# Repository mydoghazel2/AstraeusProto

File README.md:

# Astraeus

This is the github repo of the West Virginia University SRAD avionics project named Astraeus.

Astreaus is a student led project to develop cheap, open-source, and modular avionics. The goal is to create electronics for our competition rocket and for student use on personal rockets. 

Astraeus is the greek god of the wind and dusk to match not only the idea of our avionics being on a rocket but also our competition rocket being named "Dark and Dusty" after the song Country Roads 

# Final Design 
## Top Side

## Bottom Side 

# PCB

EAGLE is used as the PCB designing software. All the libraries needed is included in `./PCB/lib`

- if you are on linux. Use the following command to make a sim links to the default eagle save directory  

```
ln -s ./PCB $HOME/EAGLE/projects/git-pcb
```

- if you are on windows 10: Add instructions on how to get EAGLE running

# TO-DO

- [x] Initial planning and requirement gathering.
- [x] Finalizing the hardware specification.
- [x] Schematic design
  - [x] BMS
  - [x] voltage regulation
  - [x] Sensors
  - [x] USB
  - [ ] upload/download
  - [ ] SD card

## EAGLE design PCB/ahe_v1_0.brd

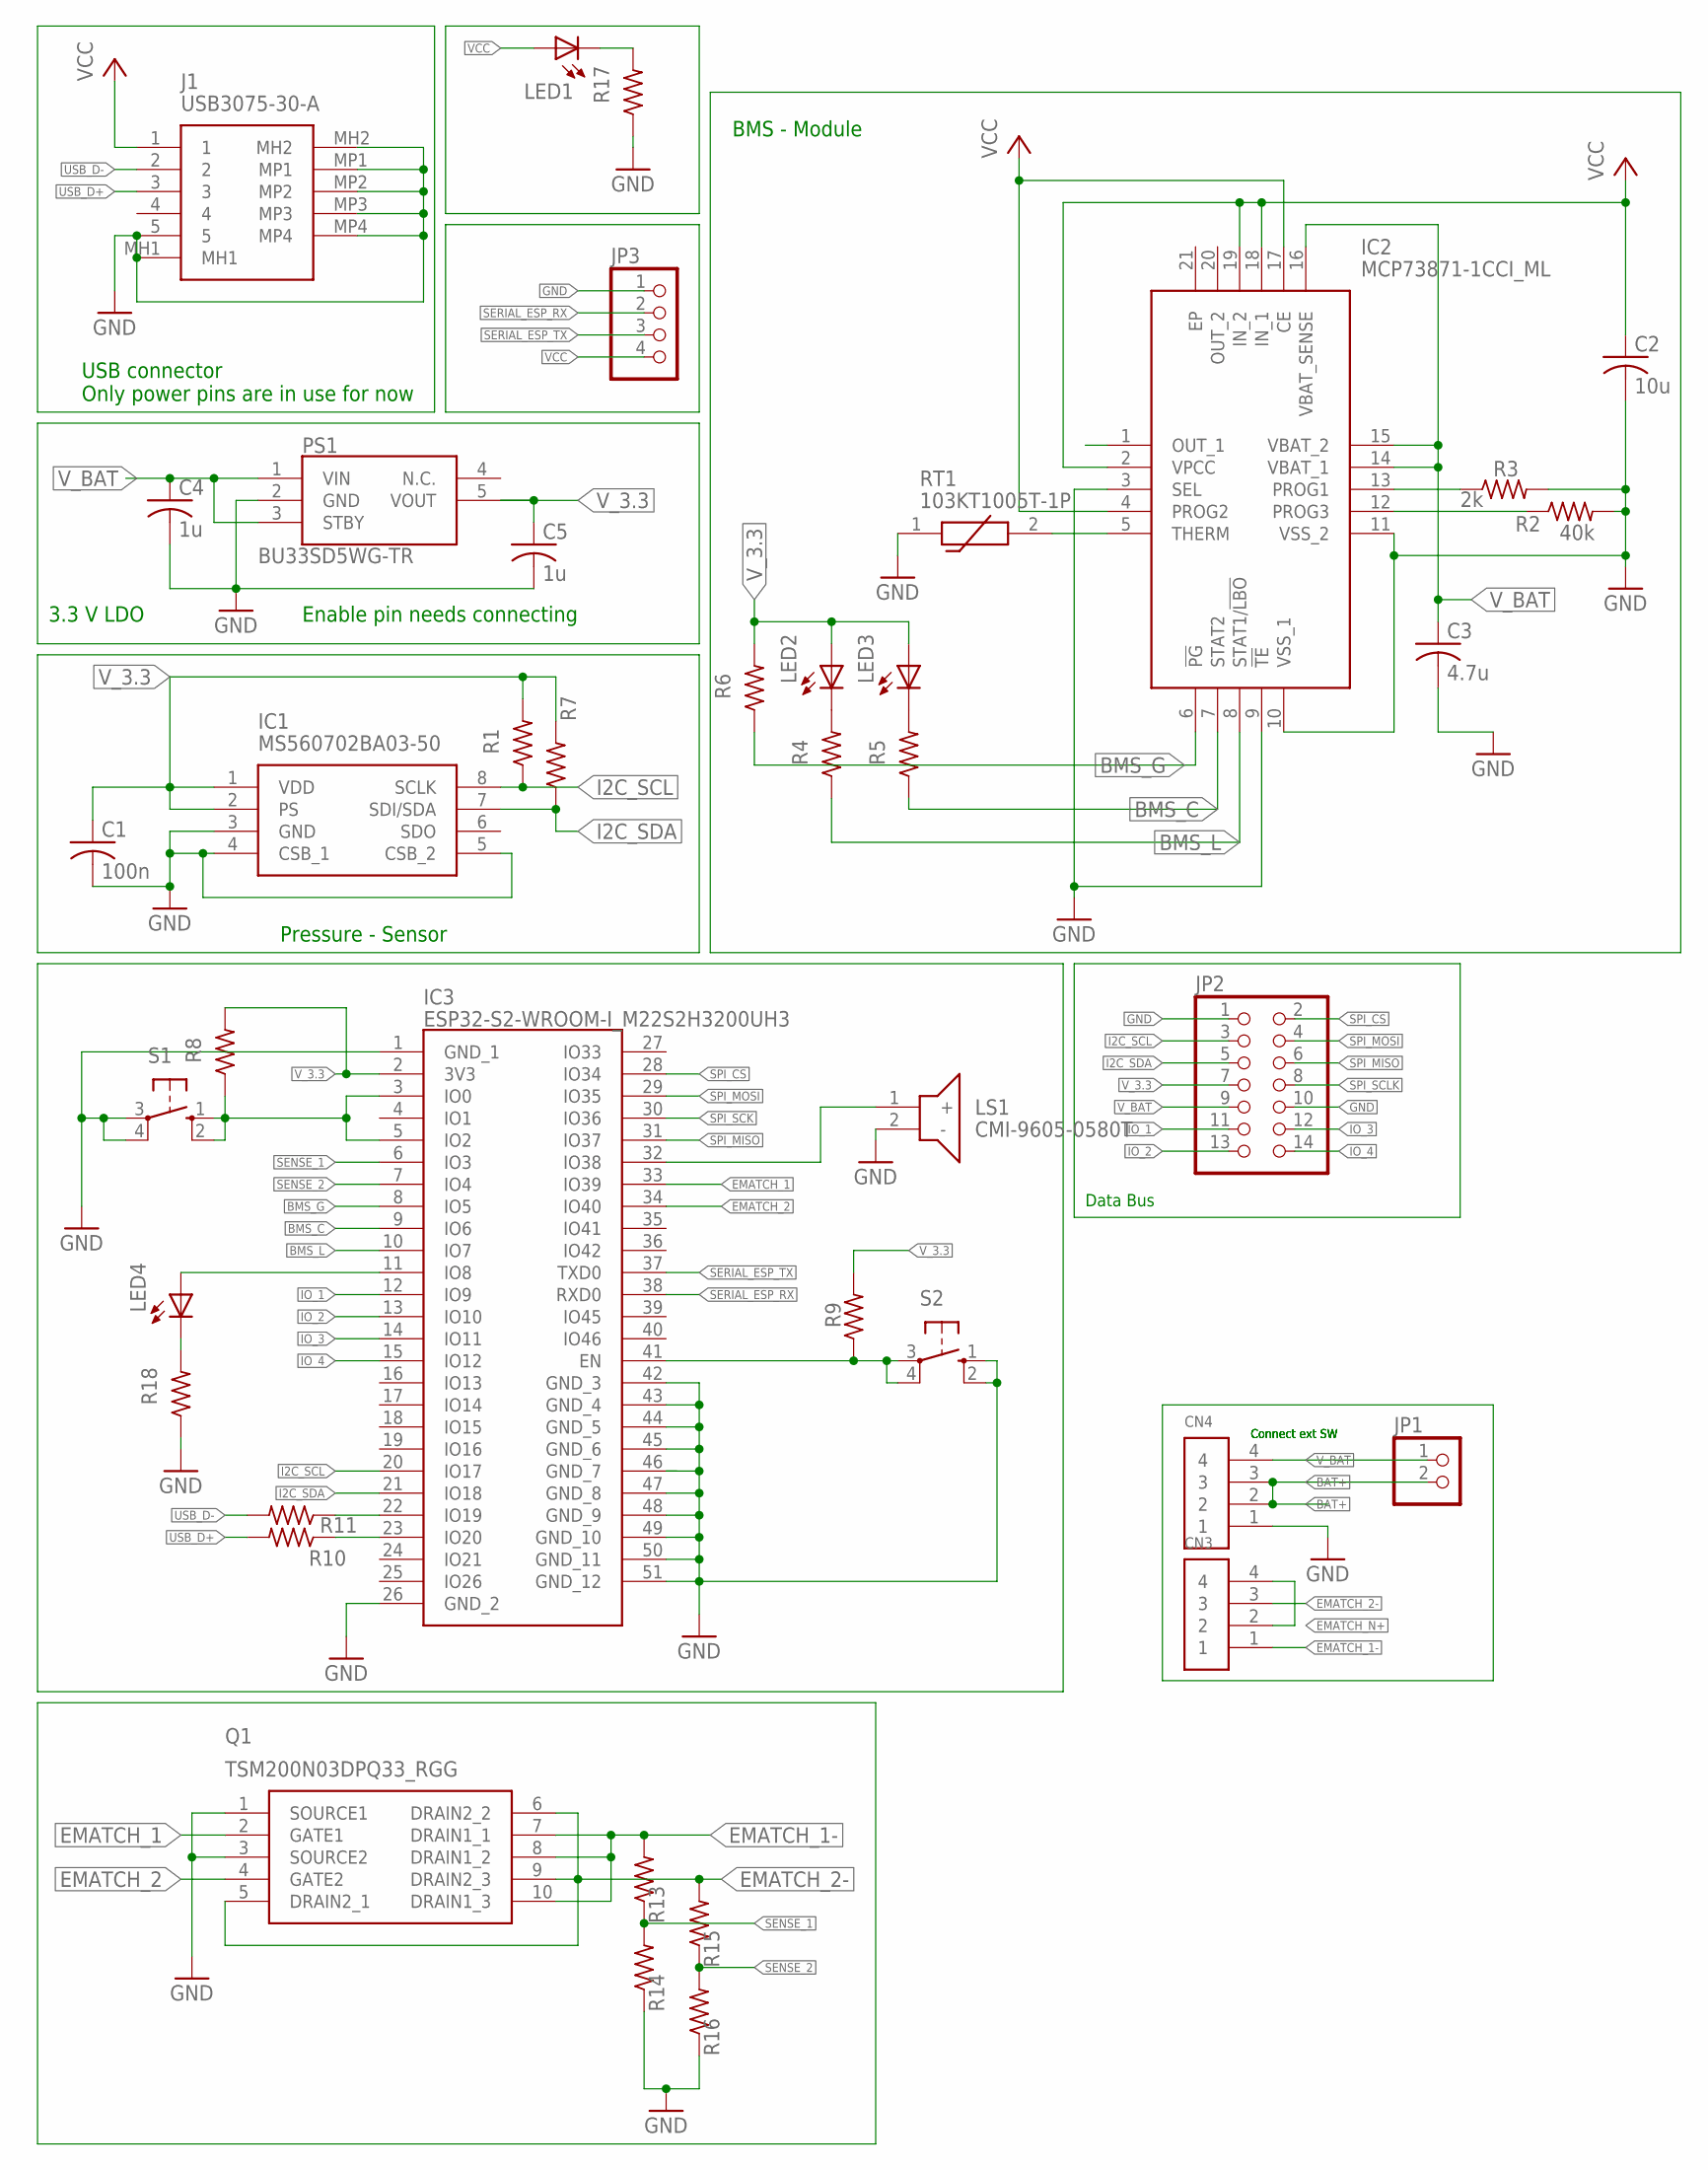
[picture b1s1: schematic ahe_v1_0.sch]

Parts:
C1: 100n; C0805
C2: 10u; C0805
C3: 4.7u; C0805
C4, C5: 1u; C0805
CN3, CN4: 1X4-3.5MM; 1X04-3.5MM
IC1: MS560702BA03-50; MS5607-02BA03
IC2: MCP73871-1CCI_ML; QFN50P400X400X100-21N
IC3: ESP32-S2-WROOM-I_M22S2H3200UH3; ESP32S2WROOMIM22S2H3200UH3Q0
J1: USB3075-30-A; USB307530A
JP1: PINHD-1X2; 1X02
JP2: PINHD-2X7; 2X07
JP3: PINHD-1X4/90; 1X04/90
LED1, LED2, LED3, LED4: LEDCHIPLED_0805; CHIPLED_0805
LS1: CMI-9605-0580T; CMI96050580T
PS1: BU33SD5WG-TR; SOT95P280X125-5N
Q1: TSM200N03DPQ33_RGG; TSM200N03DPQ33RGG
R1, R6, R7, R8, R9: 10k; R0805
R2: 40k; R0805
R3: 2k; R0805
R4, R5, R17, R18: 330; R0805
R10, R11: 33; R0805
R13, R15: 100k; R0805
R14, R16: 27k; R0805
RT1: 103KT1005T-1P; THRMC1005X60N
S1, S2: 10-XX; B3F-10XX

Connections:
BAT+: CN4.2, CN4.3, JP1.2
BMS_C: IC2.7 (STAT2), IC3.9 (IO6), R5.1
BMS_G: IC2.6 (!PG), IC3.8 (IO5), R6.1
BMS_L: IC2.8 (STAT1/!LBO), IC3.10 (IO7), R4.1
EMATCH_1: IC3.33 (IO39), Q1.2 (GATE1)
EMATCH_1-: CN3.1, Q1.7 (DRAIN1_1), Q1.8 (DRAIN1_2), Q1.10 (DRAIN1_3), R13.2
EMATCH_2: IC3.34 (IO40), Q1.4 (GATE2)
EMATCH_2-: CN3.3, Q1.5 (DRAIN2_1), Q1.6 (DRAIN2_2), Q1.9 (DRAIN2_3), R15.2
EMATCH_N+: CN3.2, CN3.4
I2C_SCL: IC1.8 (SCLK), IC3.20 (IO17), JP2.3, R1.1
I2C_SDA: IC1.7 (SDI/SDA), IC3.21 (IO18), JP2.5, R7.1
IO_1: IC3.12 (IO9), JP2.11
IO_2: IC3.13 (IO10), JP2.13
IO_3: IC3.14 (IO11), JP2.12
IO_4: IC3.15 (IO12), JP2.14
unnamed: IC2.13 (PROG1), R3.1
unnamed: IC2.12 (PROG3), R2.1
unnamed 17: IC2.5 (THERM), RT1.2; also elsewhere on the board
unnamed: IC3.3 (IO0), IC3.5 (IO2), R8.1, S1.1 (S), S1.2 (S1)
unnamed: IC3.22 (IO19), R11.1
unnamed: IC3.23 (IO20), R10.1
unnamed: LED1.C, R17.2
unnamed: LED2.C, R4.2
unnamed: LED3.C, R5.2
unnamed: LED4.C, R18.2
unnamed: IC3.11 (IO8), LED4.A
SENSE_1: IC3.6 (IO3), R13.1, R14.2
SENSE_2: IC3.7 (IO4), R15.1, R16.2
SERIAL_ESP_RX: IC3.38 (RXD0), JP3.2; also elsewhere on the board
SERIAL_ESP_TX: IC3.37 (TXD0), JP3.3; also elsewhere on the board
SOUND: IC3.32 (IO38), LS1.1 (+)
SPI_CS: IC3.28 (IO34), JP2.2
SPI_MISO: IC3.31 (IO37), JP2.6
SPI_MOSI: IC3.29 (IO35), JP2.4
SPI_SCK: IC3.30 (IO36)
SPI_SCLK: JP2.8
USB_D+: J1.3, R10.2
USB_D-: J1.2, R11.2
VCC: C2.1, IC2.2 (VPCC), IC2.4 (PROG2), IC2.17 (CE), IC2.18 (IN_1), IC2.19 (IN_2), J1.1, JP3.4, LED1.A; also elsewhere on the board
V_3.3: C1.1, C5.1, IC1.1 (VDD), IC1.2 (PS), IC3.2 (3V3), JP2.7, LED2.A, LED3.A, PS1.5 (VOUT), R1.2, R6.2, R7.2, R8.2, R9.2
V_BAT: C3.1, C4.1, CN4.4, IC2.14 (VBAT_1), IC2.15 (VBAT_2), IC2.16 (VBAT_SENSE), JP1.1, JP2.9, PS1.1 (VIN), PS1.3 (STBY)

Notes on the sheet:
Pressure - Sensor
Enable pin needs connecting
USB connector Only power pins are in use for now
3.3 V LDO
BMS - Module
Data Bus
Connect ext SW

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
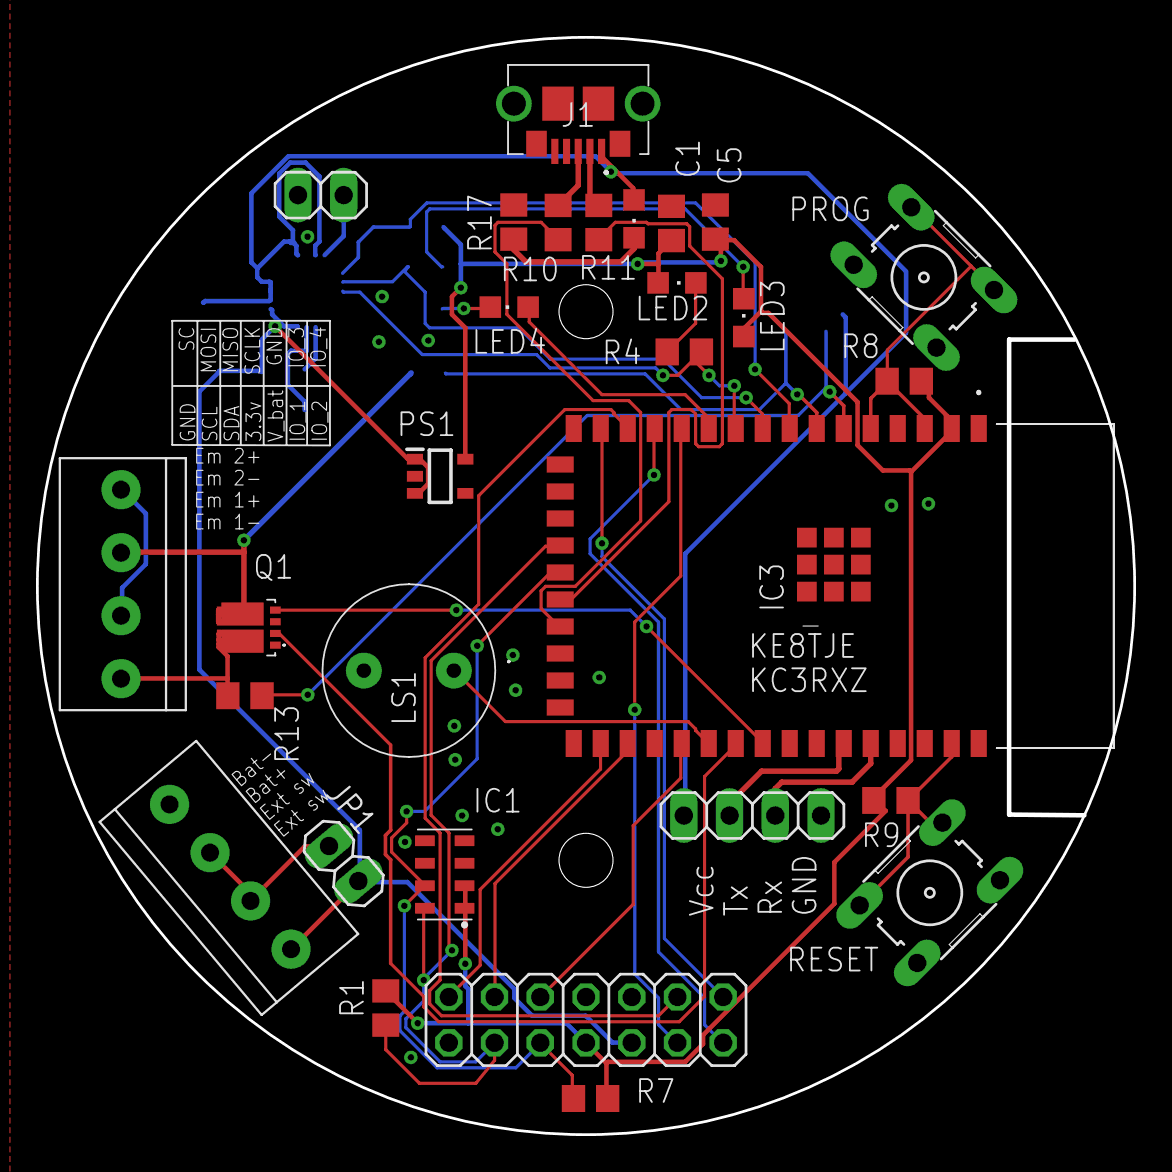
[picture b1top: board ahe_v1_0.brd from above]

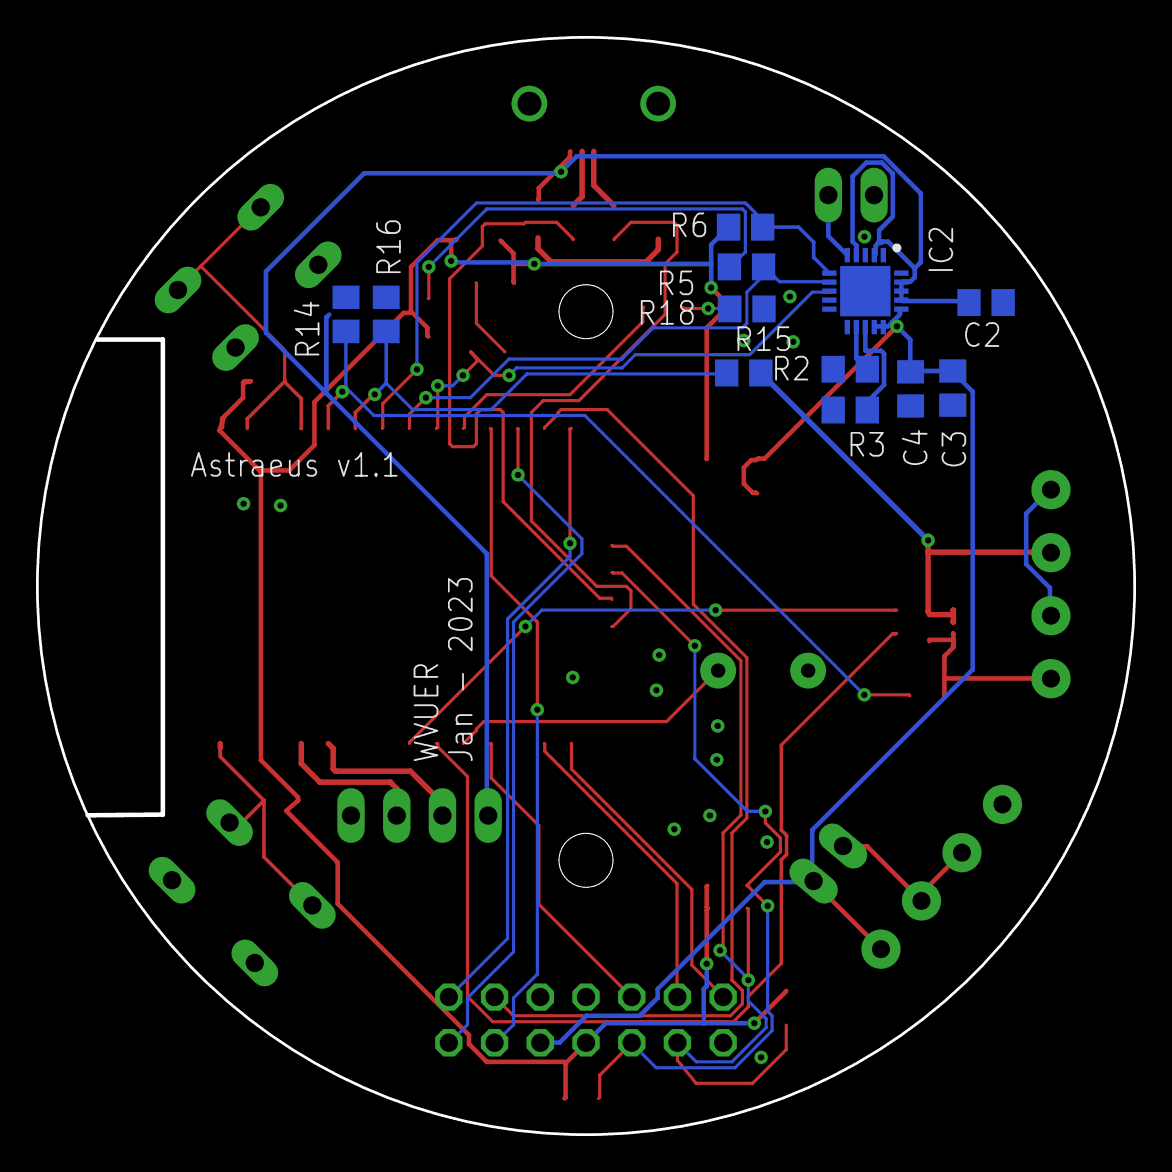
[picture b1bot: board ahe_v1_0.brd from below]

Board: 2 copper layers, 60.9 x 60.9 mm, 41 parts (12 on the bottom side), 41 nets.

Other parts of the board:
JP4: 1X02
JP5: 1X04

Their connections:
unnamed 17: JP4.2; also elsewhere on the board
SERIAL_ESP_RX: JP5.2; also elsewhere on the board
SERIAL_ESP_TX: JP5.3; also elsewhere on the board
VCC: JP5.4; also elsewhere on the board

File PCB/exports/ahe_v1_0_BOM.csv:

"Qty";"Value";"Device";"Package";"Parts";"Description";"ARROW_PART_NUMBER";"ARROW_PRICE-STOCK";"DESCRIPTION";"HEIGHT";"MANUFACTURER_NAME";"MANUFACTURER_PART_NUMBER";"MF";"MOUSER_PART_NUMBER";"MOUSER_PRICE-STOCK";"MOUSER_TESTING_PART_NUMBER";"MOUSER_TESTING_PRICE-STOCK";"MPN";"OC_FARNELL";"OC_NEWARK";"POPULARITY";"SPICEPREFIX";
"2";"";"10-XX";"B3F-10XX";"S1, S2";"OMRON SWITCH";"";"";"";"";"";"";"";"";"";"";"";"B3F-1000";"176432";"36M3542";"72";"";
"1";"";"PINHD-1X4/90";"1X04/90";"JP3";"PIN HEADER";"";"";"";"";"";"";"";"";"";"";"";"";"";"";"9";"";
"1";"";"PINHD-2X7";"2X07";"JP2";"PIN HEADER";"";"";"";"";"";"";"";"";"";"";"";"";"";"";"8";"";
"1";"0";"R-US_R0805";"R0805";"R12";"RESISTOR, American symbol";"";"";"";"";"";"";"";"";"";"";"";"";"";"";"85";"R";
"2";"100k";"R-US_R0805";"R0805";"R13, R15";"RESISTOR, American symbol";"";"";"";"";"";"";"";"";"";"";"";"";"";"";"85";"R";
"1";"100n";"C-USC0805";"C0805";"C1";"CAPACITOR, American symbol";"";"";"";"";"";"";"";"";"";"";"";"";"";"";"63";"C";
"1";"103KT1005T-1P";"103KT1005T-1P";"THRMC1005X60N";"RT1";"NTC Thermistors 103kohm 1% 0402";"";"";"NTC Thermistors 103kohm 1% 0402";"0.6mm";"Semitec";"103KT1005T-1P";"";"954-103KT1005T-1P";"https://www.mouser.co.uk/ProductDetail/Semitec/103KT1005T-1P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";"";"";"";"";"";"";"";
"7";"10k";"R-US_R0805";"R0805";"R1, R4, R5, R6, R7, R8, R9";"RESISTOR, American symbol";"";"";"";"";"";"";"";"";"";"";"";"";"";"";"85";"R";
"1";"10u";"C-USC0805";"C0805";"C2";"CAPACITOR, American symbol";"";"";"";"";"";"";"";"";"";"";"";"";"";"";"63";"C";
"2";"1X4-3.5MM";"1X4-3.5MM";"1X04-3.5MM";"CN1, CN2";"4-pin connector";"";"";"";"";"";"";"";"";"";"";"";"";"";"";"";"";
"2";"1u";"C-USC0805";"C0805";"C4, C5";"CAPACITOR, American symbol";"";"";"";"";"";"";"";"";"";"";"";"";"";"";"63";"C";
"2";"27k";"R-US_R0805";"R0805";"R14, R16";"RESISTOR, American symbol";"";"";"";"";"";"";"";"";"";"";"";"";"";"";"85";"R";
"1";"2k";"R-US_R0805";"R0805";"R3";"RESISTOR, American symbol";"";"";"";"";"";"";"";"";"";"";"";"";"";"";"85";"R";
"2";"33";"R-US_R0805";"R0805";"R10, R11";"RESISTOR, American symbol";"";"";"";"";"";"";"";"";"";"";"";"";"";"";"85";"R";
"1";"4.7u";"C-USC0805";"C0805";"C3";"CAPACITOR, American symbol";"";"";"";"";"";"";"";"";"";"";"";"";"";"";"63";"C";
"1";"40k";"R-US_R0805";"R0805";"R2";"RESISTOR, American symbol";"";"";"";"";"";"";"";"";"";"";"";"";"";"";"85";"R";
"1";"BU33SD5WG-TR";"BU33SD5WG-TR";"SOT95P280X125-5N";"PS1";"LDO regulator,3.3V,0.5A,standby,SSOP5 ROHM BU33SD5WG-TR, LDO Voltage Regulator, 0.5A, 3.3 V +/-2%, 1.7  6 Vin, 5-Pin SSOP";"";"";"LDO regulator,3.3V,0.5A,standby,SSOP5 ROHM BU33SD5WG-TR, LDO Voltage Regulator, 0.5A, 3.3 V +/-2%, 1.7  6 Vin, 5-Pin SSOP";"1.25mm";"ROHM Semiconductor";"BU33SD5WG-TR";"";"755-BU33SD5WG-TR";"https://www.mouser.co.uk/ProductDetail/ROHM-Semiconductor/BU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";"";"";"";"";"";"";"";
"1";"CMI-9605-0580T";"CMI-9605-0580T";"CMI96050580T";"LS1";"Piezo Buzzers & Audio Indicators buzzer, 9.6 mm x 5 mm deep, M, 5 VDC, 80 dB, Through Hole, Audio Indicator";"";"";"Piezo Buzzers & Audio Indicators buzzer, 9.6 mm x 5 mm deep, M, 5 VDC, 80 dB, Through Hole, Audio Indicator";"5mm";"CUI Inc.";"CMI-9605-0580T";"";"490-CMI-9605-0580T";"https://www.mouser.co.uk/ProductDetail/CUI-Devices/CMI-9605-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";"";"";"";"";"";"";"";
"1";"ESP32-S2-WROOM-I_M22S2H3200UH3";"ESP32-S2-WROOM-I_M22S2H3200UH3";"ESP32S2WROOMIM22S2H3200UH3Q0";"IC3";"WiFi Modules (802.11) Module ESP32-S2 WROOM IPEX ANT";"";"";"WiFi Modules (802.11) Module ESP32-S2 WROOM IPEX ANT";"3.45mm";"Espressif Systems";"ESP32-S2-WROOM-I(M22S2H3200UH3Q0)";"";"356-ESP32S2WRMI320UH";"https://www.mouser.co.uk/ProductDetail/Espressif-Systems/ESP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";"";"";"";"";"";"";"";
"1";"MCP73871-1CCI_ML";"MCP73871-1CCI_ML";"QFN50P400X400X100-21N";"IC2";"Battery Management USB/AC Battery Charger w/Pwr Mgmt";"";"";"Battery Management USB/AC Battery Charger w/Pwr Mgmt";"1mm";"Microchip";"MCP73871-1CCI/ML";"";"579-MCP73871-1CCI/ML";"https://www.mouser.co.uk/ProductDetail/Microchip-Technology-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";"";"";"";"";"";"";"";
"1";"MS560702BA03-50";"MS560702BA03-50";"MS5607-02BA03";"IC1";"MS560702BA03-50, Barometric Pressure Sensor, 1200mbar 0  3.6 V Output, 8-Pin QFN";"";"";"MS560702BA03-50, Barometric Pressure Sensor, 1200mbar 0  3.6 V Output, 8-Pin QFN";"mm";"TE Connectivity";"MS560702BA03-50";"";"824-MS560702BA03-50";"https://www.mouser.co.uk/ProductDetail/Measurement-Specialti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";"";"";"";"";"";"";"";
"1";"TSM200N03DPQ33_RGG";"TSM200N03DPQ33_RGG";"TSM200N03DPQ33RGG";"Q1";"MOSFET MOSFET, Dual, N-Ch Trench, 30V, 20A";"";"";"MOSFET MOSFET, Dual, N-Ch Trench, 30V, 20A";"0.8mm";"Taiwan Semiconductor";"TSM200N03DPQ33 RGG";"";"821-TSM200N03DPQ33RG";"https://www.mouser.co.uk/ProductDetail/Taiwan-Semiconductor/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";"";"";"";"";"";"";"";
"1";"USB3075-30-A";"USB3075-30-A";"USB307530A";"J1";"GCT (GLOBAL CONNECTOR TECHNOLOGY) - USB3075-30-A - USB Connector, Micro USB Type B, USB 2.0, Receptacle, 5 Ways, Surface Mount, Right Angle";"";"";"GCT (GLOBAL CONNECTOR TECHNOLOGY) - USB3075-30-A - USB Connector, Micro USB Type B, USB 2.0, Receptacle, 5 Ways, Surface Mount, Right Angle";"2.7mm";"GCT (GLOBAL CONNECTOR TECHNOLOGY)";"USB3075-30-A";"";"640-USB3075-30-A";"https://www.mouser.co.uk/ProductDetail/GCT/USB3075-30-A?qs=K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";"";"";"";"";"";"";"";

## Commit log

2022-09-23 Initial Commit with Proposal and Budget
2022-09-23 Fixed the readme md
2022-09-23 updated the readme with todo
2022-09-23 moved documentation to docs
2022-11-15 Added the eagel PCB project files to ./PCB
2022-11-15 updated the readme with eagle usage instructions
2022-11-15 Added the adafruit.lbr for basic components
2022-11-30 added an LDO
2022-12-01 added some cosmatics to completed parts
2022-12-09 Updated the BMS i/o
2022-12-09 modified BMS
2022-12-15 Completed BMS/LDO
2022-12-16 #6 pressure sensor completed
2022-12-17 updated the ESP32 library to match actual product
2022-12-17 remove old library
2022-12-18 #5 #2 added databus and basic IO
2022-12-18 full schematic
2022-12-18 added costing to the BOM
2022-12-20 added SPI from the ESP
2022-12-21 #2 board 1 with lipo mounted on the back
2022-12-21 added board file
2022-12-21 removed v1_1 junk version
2022-12-21 added information on the board design
2022-12-21 fixed schematic bugs in v1_0
2022-12-22 Final schematic and board for ESP32-S2
2022-12-22 Added PCB images
2022-12-22 Updated readme with images
2022-12-22 Added serial labels.
2022-12-23 updated BOM with links
2022-12-23 Added logo to silk screens
2023-01-11 fixed error on soft link for linux setup instructions
